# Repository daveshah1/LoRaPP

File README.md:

# LoRa++

Small, flexible LoRa module designed for HAB use as well as general 
long distance comms.

Features:
 * SX1276 LoRa transceiver
 * Same PCB can be used for 434MHz, 868MHz and probably other 
frequencies (different components required)
 * MMZ09312 PA for >27dBm output power (for 869.525MHz use in EU). 
Optional, can be bypassed with 0 ohm resistors if not needed.
 * SAW filter and MAAL-010704 LNA (also optional) in receive path 

Note: this is still in the fairly early design phase; the PCB design has 
not yet been checked or built.

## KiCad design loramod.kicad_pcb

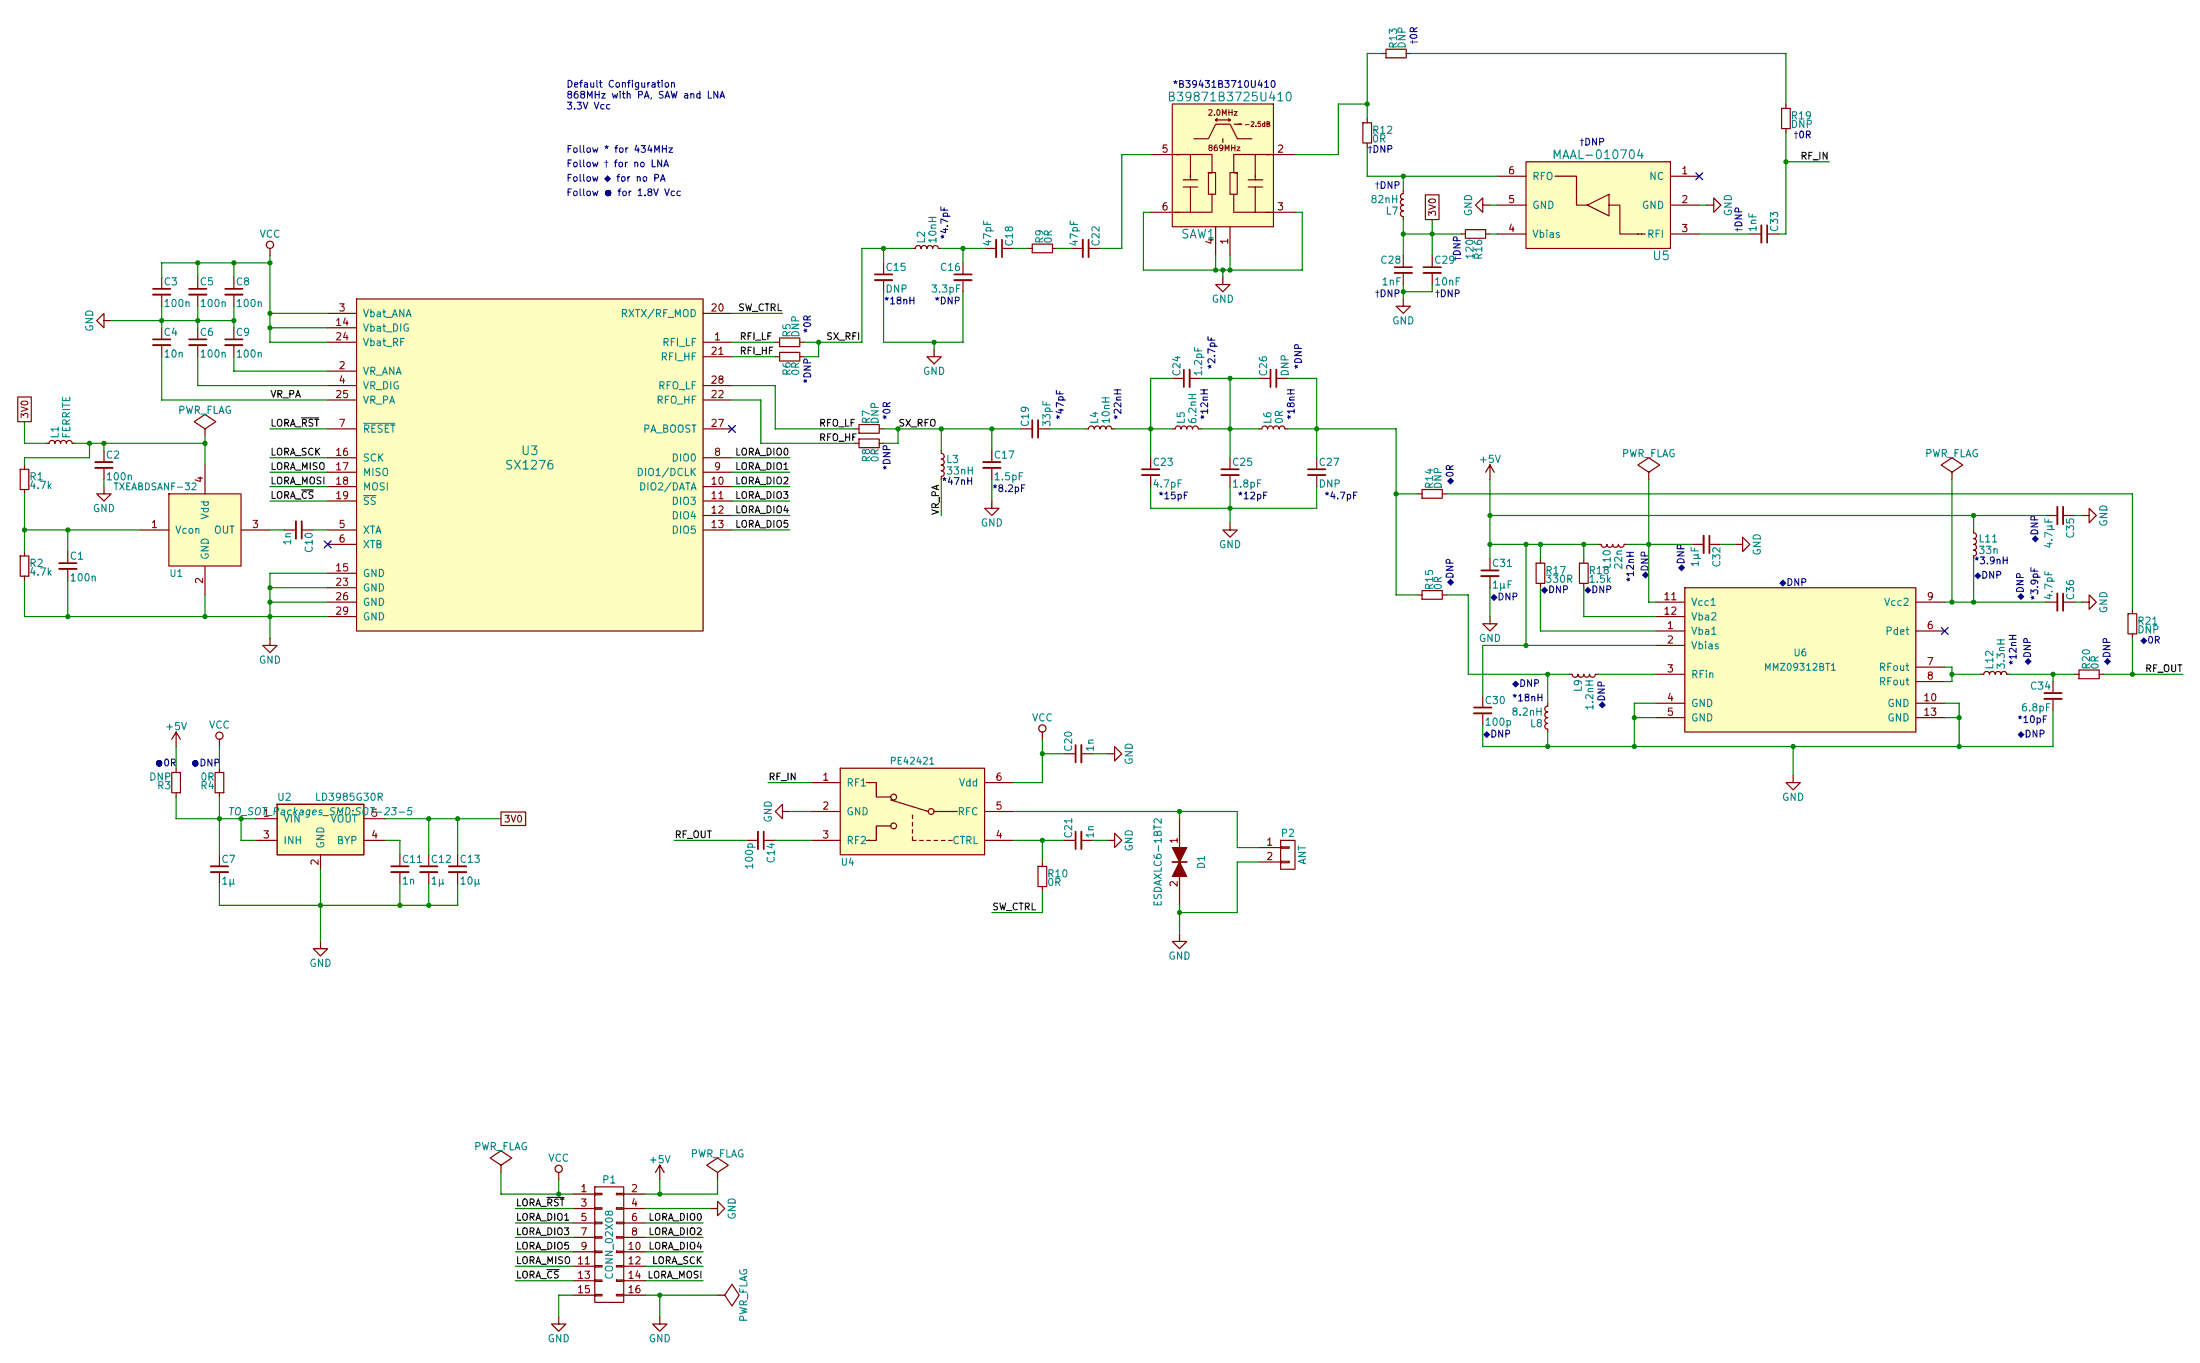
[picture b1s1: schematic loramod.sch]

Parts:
C1, C2, C3, C5, C6, C8, C9: 100n; C_0402
C4: 10n; C_0402
C7: 1µ; C_0603_HandSoldering
C10, C11, C20, C21: 1n; C_0402
C12: 1µ; C_0603
C13: 10µ; C_0805
C14, C30: 100p; C_0402
C15, C26, C27: DNP; C_0402
C16: 3.3pF; C_0402
C17: 1.5pF; C_0402
C18, C22: 47pF; C_0402
C19: 33pF; C_0402
C23, C36: 4.7pF; C_0402
C24: 1.2pF; C_0402
C25: 1.8pF; C_0402
C28, C33: 1nF; C_0402
C29: 10nF; C_0402
C31, C32: 1µF; C_0402
C34: 6.8pF; C_0402
C35: 4.7µF; C_0805
D1: ESDAXLC6-1BT2; C_0402
L1: FERRITE; R_0402
L2, L4: 10nH; R_0402
L3: 33nH; R_0402
L5: 6.2nH; R_0402
L6: 0R; R_0402
L7: 82nH; R_0402
L8: 8.2nH; R_0402
L9: 1.2nH; R_0402
L10: 22n; R_0402
L11: 33n; R_0402
L12: 3.3nH; R_0402
P1: CONN_02X08; Pin_Header_Straight_2x08_Pitch2.00mm
P2: ANT; RFcon
R1, R2: 4.7k; R_0402
R3, R5, R7, R13, R14, R19, R21: DNP; R_0402
R4, R6, R8, R9, R10, R12, R15, R20: 0R; R_0402
R16: 120; R_0402
R17: 330R; R_0402
R18: 1.5k; R_0402
SAW1: B39871B3725U410; SAW-DCC6C
U1: TXEABDSANF-32; TCXO-WT325
U2: LD3985G30R; SOT-23-5
U3: SX1276; QFN-28-1EP_6x6mm_Pitch0.65mm
U4: PE42421; SC-70-6_Handsoldering
U5: MAAL-010704; SC-70-6_Handsoldering
U6: MMZ09312BT1; QFN-12-1EP_3x3mm_Pitch0.5mm

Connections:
3V0: C12.1, C13.1, C28.1, C29.1, L1.1, L7.1, R16.2, U2.5 (VOUT)
+5V: C30.1, C31.1, C35.2, L10.1, L11.1, P1.2, R3.2, R17.1, R18.1, U6.2 (Vbias)
/LORA_DIO0: P1.6, U3.8 (DIO0)
/LORA_DIO1: P1.5, U3.9 (DIO1/DCLK)
/LORA_DIO2: P1.8, U3.10 (DIO2/DATA)
/LORA_DIO3: P1.7, U3.11 (DIO3)
/LORA_DIO4: P1.10, U3.12 (DIO4)
/LORA_DIO5: P1.9, U3.13 (DIO5)
/LORA_MISO: P1.11, U3.17 (MISO)
/LORA_MOSI: P1.14, U3.18 (MOSI)
/LORA_SCK: P1.12, U3.16 (SCK)
/LORA_~CS: P1.13, U3.19 (~SS)
/LORA_~RST: P1.3, U3.7 (~RESET)
/RFI_HF: R6.1, U3.21 (RFI_HF)
/RFI_LF: R5.1, U3.1 (RFI_LF)
/RFO_HF: R8.1, U3.22 (RFO_HF)
/RFO_LF: R7.1, U3.28 (RFO_LF)
/RF_IN: C33.1, R19.2, U4.1 (RF1)
/RF_OUT: C14.2, R20.2, R21.2
/SW_CTRL: R10.2, U3.20 (RXTX/RF_MOD)
/SX_RFI: C15.1, L2.1, R5.2, R6.2
/SX_RFO: C17.1, C19.1, L3.1, R7.2, R8.2
/VR_PA: C4.2, L3.2, U3.25 (VR_PA)
GND: C1.2, C2.2, C3.2, C4.1, C5.2, C6.1, C7.2, C8.2, C9.1, C11.2, C12.2, C13.2, C15.2, C16.2, C17.2, C20.2, C21.2, C23.2, C25.2, C27.2, C28.2, C29.2, C30.2, C31.2, C32.1, C34.2, C35.1, C36.1, D1.2, L8.1, P1.4, P1.15, P1.16, P2.2, R2.2, SAW1.1 (GND), SAW1.3 (GND), SAW1.4 (GND), SAW1.6 (GND), U1.2 (GND), U2.2 (GND), U3.15 (GND), U3.23 (GND), U3.26 (GND), U3.29 (GND), U4.2 (GND), U5.2 (GND), U5.5 (GND), U6.4 (GND), U6.5 (GND), U6.10 (GND), U6.13 (GND)
unnamed: C1.1, R1.2, R2.1, U1.1 (Vcon)
unnamed: C2.1, L1.2, R1.1, U1.4 (Vdd)
unnamed: C6.2, U3.4 (VR_DIG)
unnamed: C7.1, R3.1, R4.1, U2.1 (VIN), U2.3 (INH)
unnamed: C9.2, U3.2 (VR_ANA)
unnamed: C10.1, U3.5 (XTA)
unnamed: C10.2, U1.3 (OUT)
unnamed: C11.1, U2.4 (BYP)
unnamed: C14.1, U4.3 (RF2)
unnamed: C16.1, C18.2, L2.2
unnamed: C18.1, R9.1
unnamed: C19.2, L4.1
unnamed: C21.1, R10.1, U4.4 (CTRL)
unnamed: C22.1, SAW1.5 (OUT)
unnamed: C22.2, R9.2
unnamed: C23.1, C24.1, L4.2, L5.1
unnamed: C24.2, C25.1, C26.1, L5.2, L6.1
unnamed: C26.2, C27.1, L6.2, R14.1, R15.1
unnamed: C32.2, L10.2, U6.11 (Vcc1)
unnamed: C33.2, U5.3 (RFI)
unnamed: C34.1, L12.2, R20.1
unnamed: C36.2, L11.2, U6.9 (Vcc2)
unnamed: D1.1, P2.1, U4.5 (RFC)
unnamed: L7.2, R12.2, U5.6 (RFO)
unnamed: L8.2, L9.1, R15.2
unnamed: L9.2, U6.3 (RFin)
unnamed: L12.1, U6.7 (RFout), U6.8 (RFout)
unnamed: R12.1, R13.1, SAW1.2 (IN)
unnamed: R13.2, R19.1
unnamed: R14.2, R21.1
unnamed: R16.1, U5.4 (Vbias)
unnamed: R17.2, U6.1 (Vba1)
unnamed: R18.2, U6.12 (Vba2)
VCC: C3.1, C5.1, C8.1, C20.1, P1.1, R4.2, U3.3 (Vbat_ANA), U3.14 (Vbat_DIG), U3.24 (Vbat_RF), U4.6 (Vdd)

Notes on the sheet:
*18nH
*DNP
*4.7pF
*DNP
*0R
*B39431B3710U410
Default Configuration 868MHz with PA, SAW and LNA 3.3V Vcc
Follow * for 434MHz
Follow † for no LNA
†0R
†DNP
*47nH
*8.2pF
*47pF
*22nH
*15pF
*12pF
*12nH
*2.7pF
*10pF
*3.9nH
*3.9pF
◆0R
◆DNP
Follow ◆ for no PA
Follow ● for 1.8V Vcc
●0R
●DNP

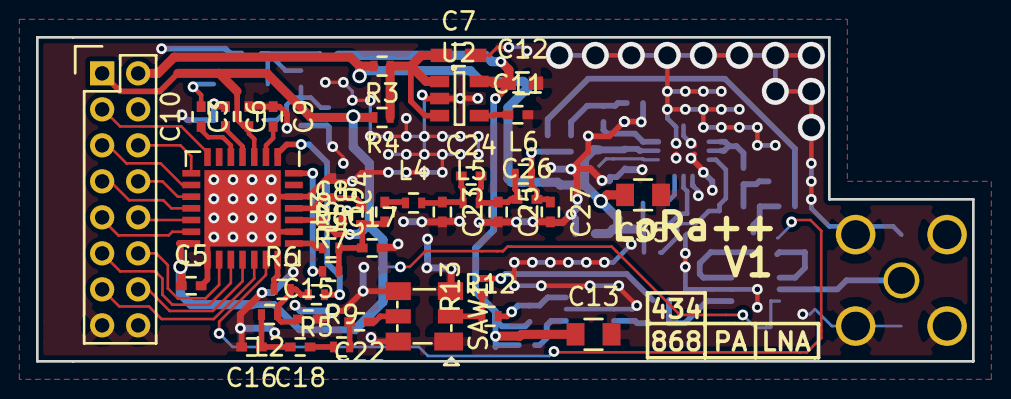
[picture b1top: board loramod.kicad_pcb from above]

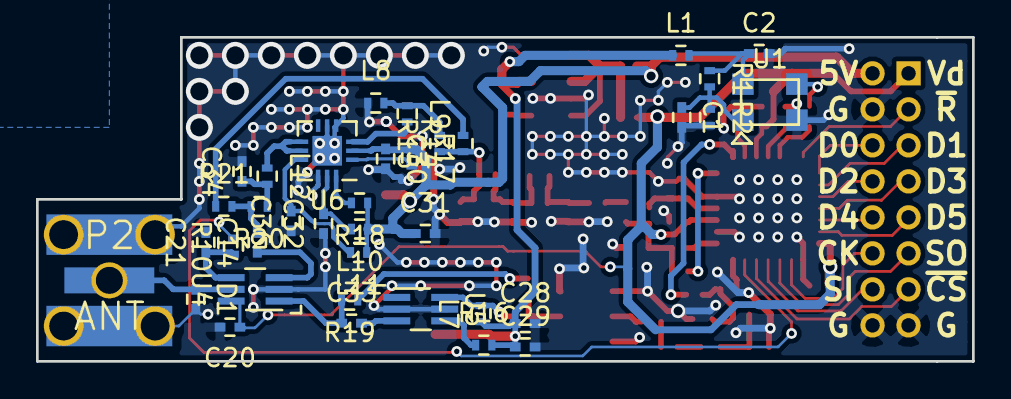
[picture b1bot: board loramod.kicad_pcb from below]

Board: 4 copper layers, 52.0 x 18.0 mm, 78 parts (37 on the bottom side), 58 nets.

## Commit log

2016-09-14 Initial design with SX1276 and rx path
2016-09-14 Add PA in Tx path
2016-09-14 Add RF switch
2016-09-14 Add IO connector; annotate schematic
2016-09-14 Start placing PCB parts
2016-09-14 PCB part placement done
2016-09-14 All tracks routed, need to create ground planes
2016-09-14 Finish PCB attempt 1; add README
2016-09-14 Modify PCB design to fit with Elecrow's 5cm limit
